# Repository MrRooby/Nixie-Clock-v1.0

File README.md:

# Nixie Clock v1.0

An ESP32-based Nixie Clock project featuring:
- Time and date display
- Temperature and humidity readings
- Gas level alarm detection
- Bluetooth control for alarm clock

## Table of Contents
1. [Introduction](#introduction)
2. [Features](#features)
3. [Hardware Setup](#hardware-setup)
4. [Bluetooth Application](#bluetooth-application)
5. [Schematic and Board Photos](#schematic-and-board-photos)
6. [Device Photos](#device-photos)
7. [**Issues**](#issues)

## Introduction
This project displays the current time, date, temperature, and humidity on Z573M Nixie tubes. It also includes a gas sensor alarm, and Bluetooth set alarm clock connectivity.

## Features
- Displays time in HH:MM format on Nixie tubes
- Shows date in DD-MM format
- Reads temperature and humidity via a DHT22 sensor
- Detects gas levels using an MQ-9 sensor
- Allows alarm configuration via Bluetooth
- Alerts with a buzzer and LEDs

## Hardware Setup
1. Nixie tubes are connected to 170V and are driven via K155ID.
2. Drivers responsible for the lamps are connected to ESP32 via Level Shifters (3.3V to 5V)
3. Two of the drivers are connected to PCF8575 I2C port expander.
4. RTC clock is connected to the board for time keeping
5. DHT and MQ-9 sensors are connected directly to the ESP32 pins.
6. Buzzer and LEDs are connected directly to the ESP32

## Bluetooth Application
*(pending)*

## Schematic and Board Photos

## Device Photos

## Issues
The device's current version suffers from a couple of mistakes or errors.
1. Mirrored Z573M library. **Temporary fix:** Lamps connected from the bottom of the board.
2. Board enters boot-loop. **Temporary fix:** Button connected between IO12 and GND. If pressed, the board exits the boot loop and functions properly.
3. Wrong MQ9 input voltage. Sensor requires 5V and connected trace supplies 3.3V. **Temporary fix:** Cable connected to 5V omitting on-board trace.
4. LED pins don't supply enough current via PCF8575 **Temporary fix:** LEDs connected directly to ESP32

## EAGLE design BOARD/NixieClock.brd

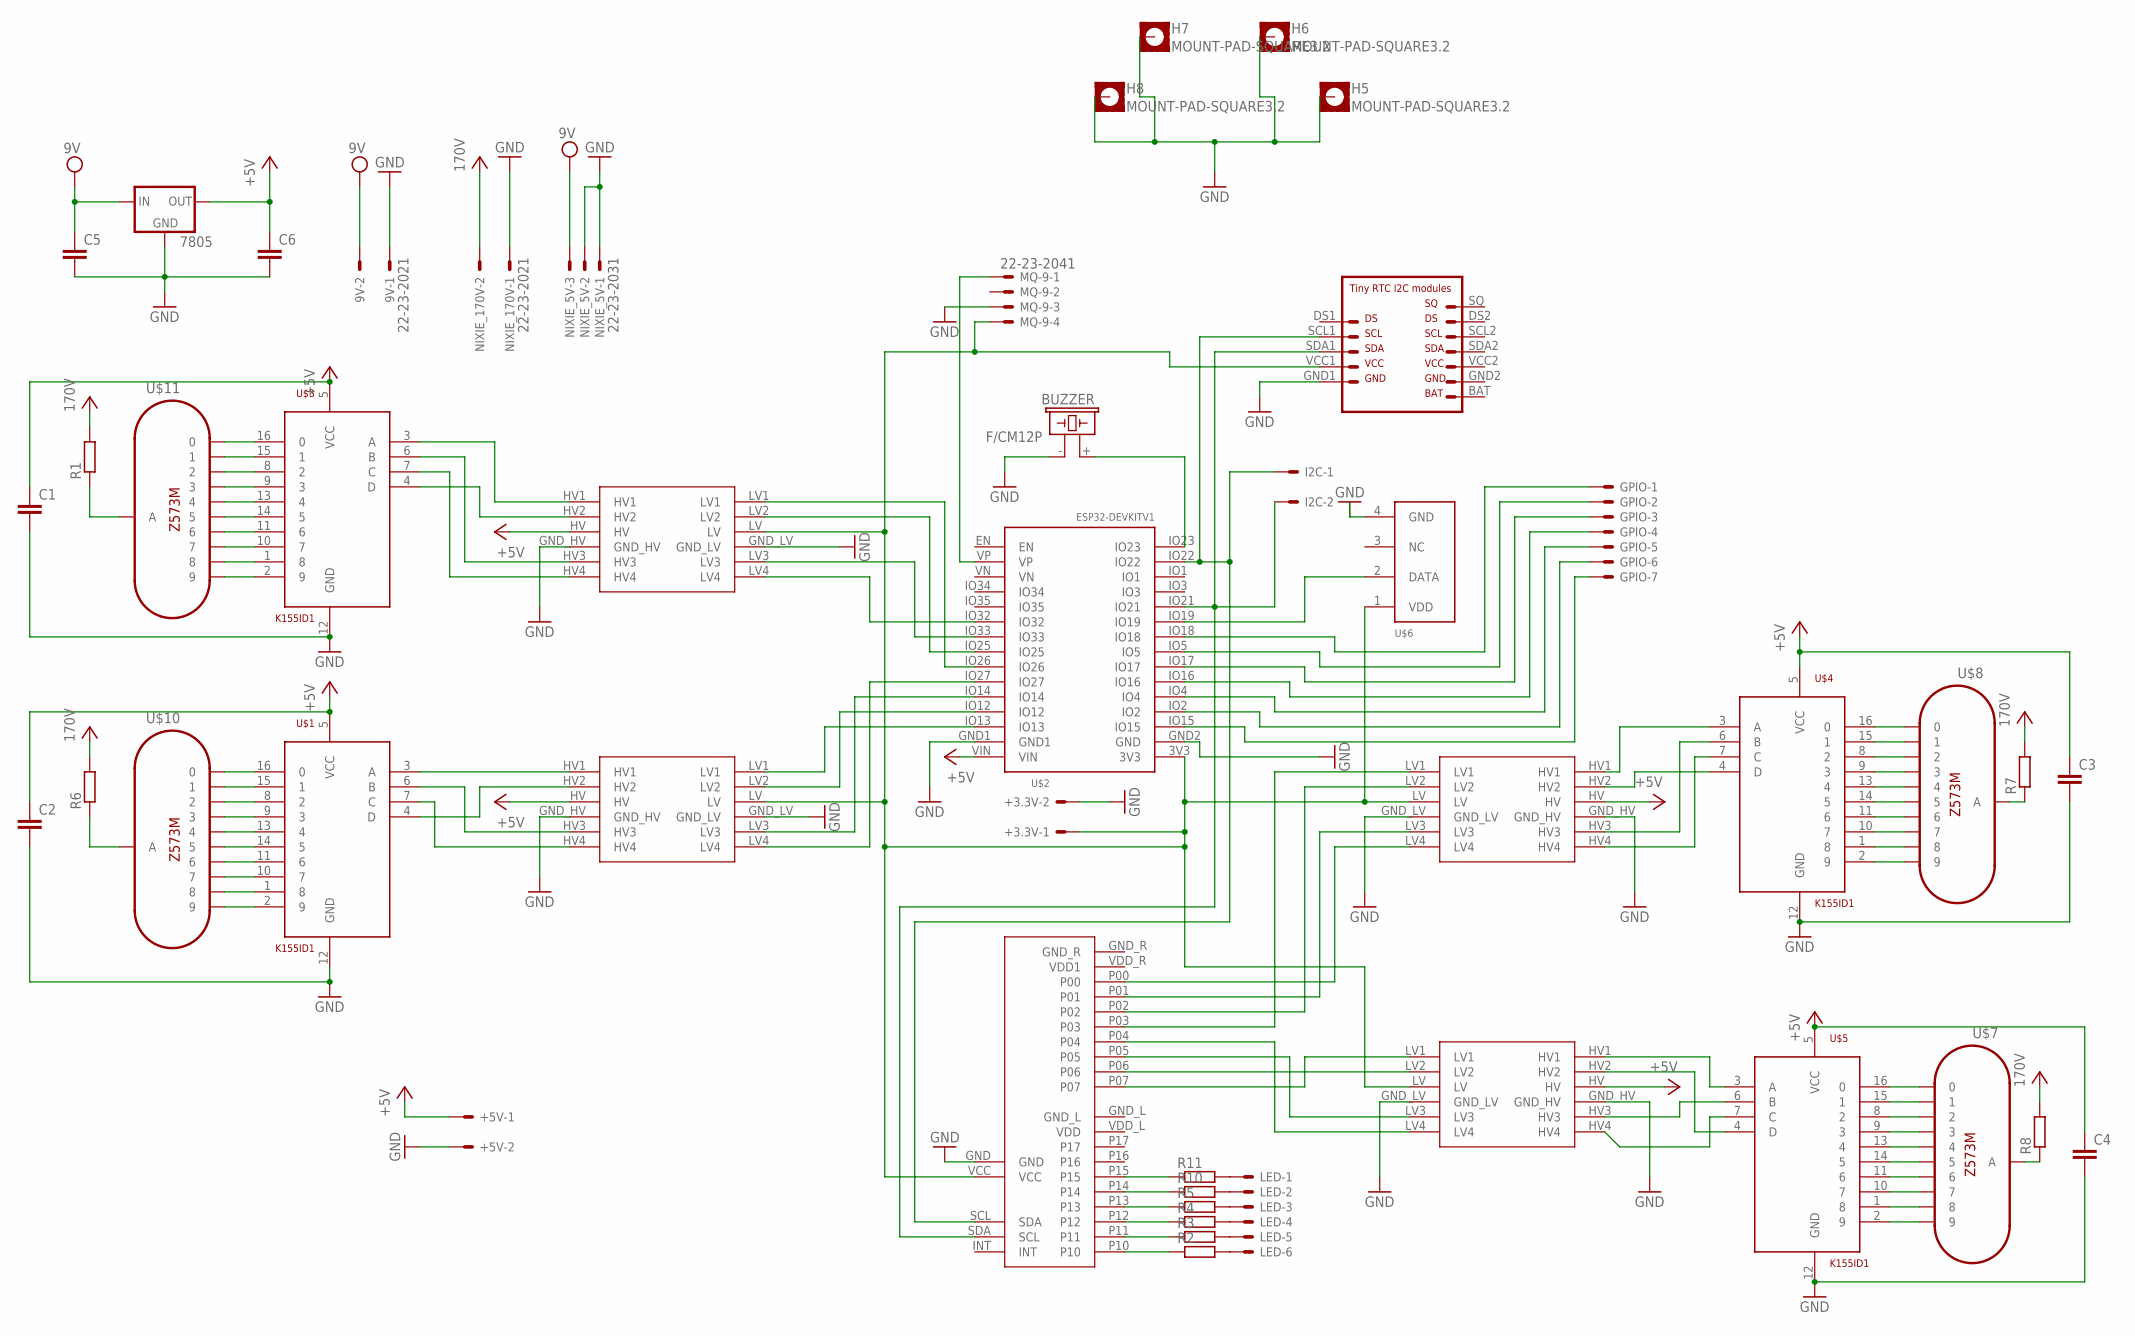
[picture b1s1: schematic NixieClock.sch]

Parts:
9V: 22-23-2021
7805: 78XXS
+3.3V, +5V: KK-156-2
BUZZER: F/CM12P
C1, C2, C3, C4, C5, C6: C2,5-3; C2.5-3
GPIO: KK-156-7
H5, H6, H7, H8: MOUNT-PAD-SQUARE3.2; 3,2-PAD-SQUARE
I2C: KK-156-2
LED: KK-156-6
MQ-9: 22-23-2041; MPN wyświetlacz I2C
NIXIE_5V: 22-23-2031
NIXIE_170V: 22-23-2021
R1, R2, R3, R4, R5, R6, R7, R8, R10, R11: R-EU_0204/7; 0204/7
STEP_UP_$: LEVEL-CONVERTER
U$1, U$3, U$4, U$5: K155ID1; DIP16-2.54-19.2X7.62MM
U$2: ESP32DEVKITV1; ESP32-DEVKITV1
U$6: DHT11
U$7, U$8, U$10, U$11: Z573M
U$9: RTC
U$12, U$13, U$15: LEVEL-CONVERTER
U$16: PCF8575

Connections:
3.3V: +3.3V.1, MQ-9.4, STEP_UP_$.LV, U$2.3V3, U$6.1 (VDD), U$9.VCC1, U$12.LV, U$13.LV, U$15.LV, U$16.VCC
170V: 9V.2, 7805.IN, C5.1, NIXIE_5V.3, NIXIE_170V.2, R1.2, R6.2, R7.2, R8.2
+5V: 7805.OUT, +5V.1, C1.1, C2.1, C3.1, C4.1, C6.1, STEP_UP_$.HV, U$1.5 (VCC), U$2.VIN, U$3.5 (VCC), U$4.5 (VCC), U$5.5 (VCC), U$12.HV, U$13.HV, U$15.HV
GND: 9V.1, 7805.GND, +3.3V.2, +5V.2, BUZZER.- (2), C1.2, C2.2, C3.2, C4.2, C5.2, C6.2, H5.B3,2, H6.B3,2, H7.B3,2, H8.B3,2, MQ-9.3, NIXIE_5V.1, NIXIE_5V.2, NIXIE_170V.1, STEP_UP_$.GND_HV, STEP_UP_$.GND_LV, U$1.12 (GND), U$2.GND1, U$2.GND2 (GND), U$3.12 (GND), U$4.12 (GND), U$5.12 (GND), U$6.4 (GND), U$9.GND1, U$12.GND_HV, U$12.GND_LV, U$13.GND_HV, U$13.GND_LV, U$15.GND_HV, U$15.GND_LV, U$16.GND
unnamed: STEP_UP_$.HV1, U$5.3 (A)
unnamed: STEP_UP_$.HV2, U$5.4 (D)
unnamed: STEP_UP_$.HV3, U$5.6 (B)
unnamed: STEP_UP_$.HV4, U$5.7 (C)
unnamed: U$15.LV4, U$16.P00
unnamed: U$4.3 (A), U$15.HV1
unnamed: U$4.4 (D), U$15.HV2
unnamed: U$4.6 (B), U$15.HV3
unnamed: U$3.3 (A), U$13.HV1
unnamed: U$3.4 (D), U$13.HV2
unnamed: U$3.6 (B), U$13.HV3
unnamed: U$3.7 (C), U$13.HV4
unnamed: U$1.3 (A), U$12.HV1
unnamed: U$1.4 (D), U$12.HV2
unnamed: U$1.6 (B), U$12.HV3
unnamed: U$1.7 (C), U$12.HV4
unnamed: U$3.16 (0), U$11.K0 (0)
unnamed: U$3.15 (1), U$11.K1 (1)
unnamed: U$3.8 (2), U$11.K2 (2)
unnamed: U$3.9 (3), U$11.K3 (3)
unnamed: U$3.13 (4), U$11.K4 (4)
unnamed: U$3.14 (5), U$11.K5 (5)
unnamed: U$3.11 (6), U$11.K6 (6)
unnamed: U$3.10 (7), U$11.K7 (7)
unnamed: U$3.1 (8), U$11.K8 (8)
unnamed: U$3.2 (9), U$11.K9 (9)
unnamed: U$1.16 (0), U$10.K0 (0)
unnamed: U$1.15 (1), U$10.K1 (1)
unnamed: U$1.8 (2), U$10.K2 (2)
unnamed: U$1.9 (3), U$10.K3 (3)
unnamed: U$1.13 (4), U$10.K4 (4)
unnamed: U$1.14 (5), U$10.K5 (5)
unnamed: U$1.11 (6), U$10.K6 (6)
unnamed: U$1.10 (7), U$10.K7 (7)
unnamed: U$1.1 (8), U$10.K8 (8)
unnamed: U$1.2 (9), U$10.K9 (9)
unnamed: U$5.16 (0), U$7.K0 (0)
unnamed: U$5.15 (1), U$7.K1 (1)
unnamed: U$5.8 (2), U$7.K2 (2)
unnamed: U$5.9 (3), U$7.K3 (3)
unnamed: U$5.13 (4), U$7.K4 (4)
unnamed: U$5.14 (5), U$7.K5 (5)
unnamed: U$5.11 (6), U$7.K6 (6)
unnamed: U$5.10 (7), U$7.K7 (7)
unnamed: U$5.1 (8), U$7.K8 (8)
unnamed: U$5.2 (9), U$7.K9 (9)
unnamed: U$4.2 (9), U$8.K9 (9)
unnamed: U$4.1 (8), U$8.K8 (8)
unnamed: U$4.10 (7), U$8.K7 (7)
unnamed: U$4.11 (6), U$8.K6 (6)
unnamed: U$4.14 (5), U$8.K5 (5)
unnamed: U$4.13 (4), U$8.K4 (4)
unnamed: U$4.9 (3), U$8.K3 (3)
unnamed: U$4.8 (2), U$8.K2 (2)
unnamed: U$4.15 (1), U$8.K1 (1)
unnamed: U$4.16 (0), U$8.K0 (0)
unnamed: U$15.LV3, U$16.P01
unnamed: U$2.IO27, U$12.LV4
unnamed: I2C.1, U$2.IO22, U$9.SCL1, U$16.SCL (SDA)
unnamed: I2C.2, U$2.IO21, U$9.SDA1, U$16.SDA (SCL)
unnamed: BUZZER.+ (1), U$2.IO23
unnamed: U$15.LV2, U$16.P02
unnamed: MQ-9.1, U$2.VP
unnamed: U$15.LV1, U$16.P03
unnamed: STEP_UP_$.LV4, U$16.P04
unnamed: STEP_UP_$.LV3, U$16.P05
unnamed: STEP_UP_$.LV2, U$16.P06
unnamed: STEP_UP_$.LV1, U$16.P07
unnamed: U$2.IO19, U$6.2 (DATA)
unnamed: GPIO.1, U$2.IO18
unnamed: GPIO.2, U$2.IO5
unnamed: U$2.IO26, U$13.LV1
unnamed: U$2.IO25, U$13.LV2
unnamed: U$2.IO33, U$13.LV3
unnamed: U$2.IO32, U$13.LV4
unnamed: U$2.IO13, U$12.LV1
unnamed: U$2.IO12, U$12.LV2
unnamed: U$2.IO14, U$12.LV3
unnamed: R8.1, U$7.A
unnamed: R7.1, U$8.A
unnamed: R6.1, U$10.A
unnamed: R1.1, U$11.A
unnamed: GPIO.3, U$2.IO17
unnamed: R2.1, U$16.P10
unnamed: R3.1, U$16.P11
unnamed: R4.1, U$16.P12
unnamed: R5.1, U$16.P13
unnamed: R10.1, U$16.P14
unnamed: R11.1, U$16.P15
unnamed: LED.1, R11.2
unnamed: LED.2, R10.2
unnamed: LED.3, R5.2
unnamed: LED.4, R4.2
unnamed: LED.5, R3.2
unnamed: LED.6, R2.2
unnamed: GPIO.4, U$2.IO16
unnamed: GPIO.5, U$2.IO4
unnamed: GPIO.6, U$2.IO2
unnamed: GPIO.7, U$2.IO15
unnamed: U$4.7 (C), U$15.HV4

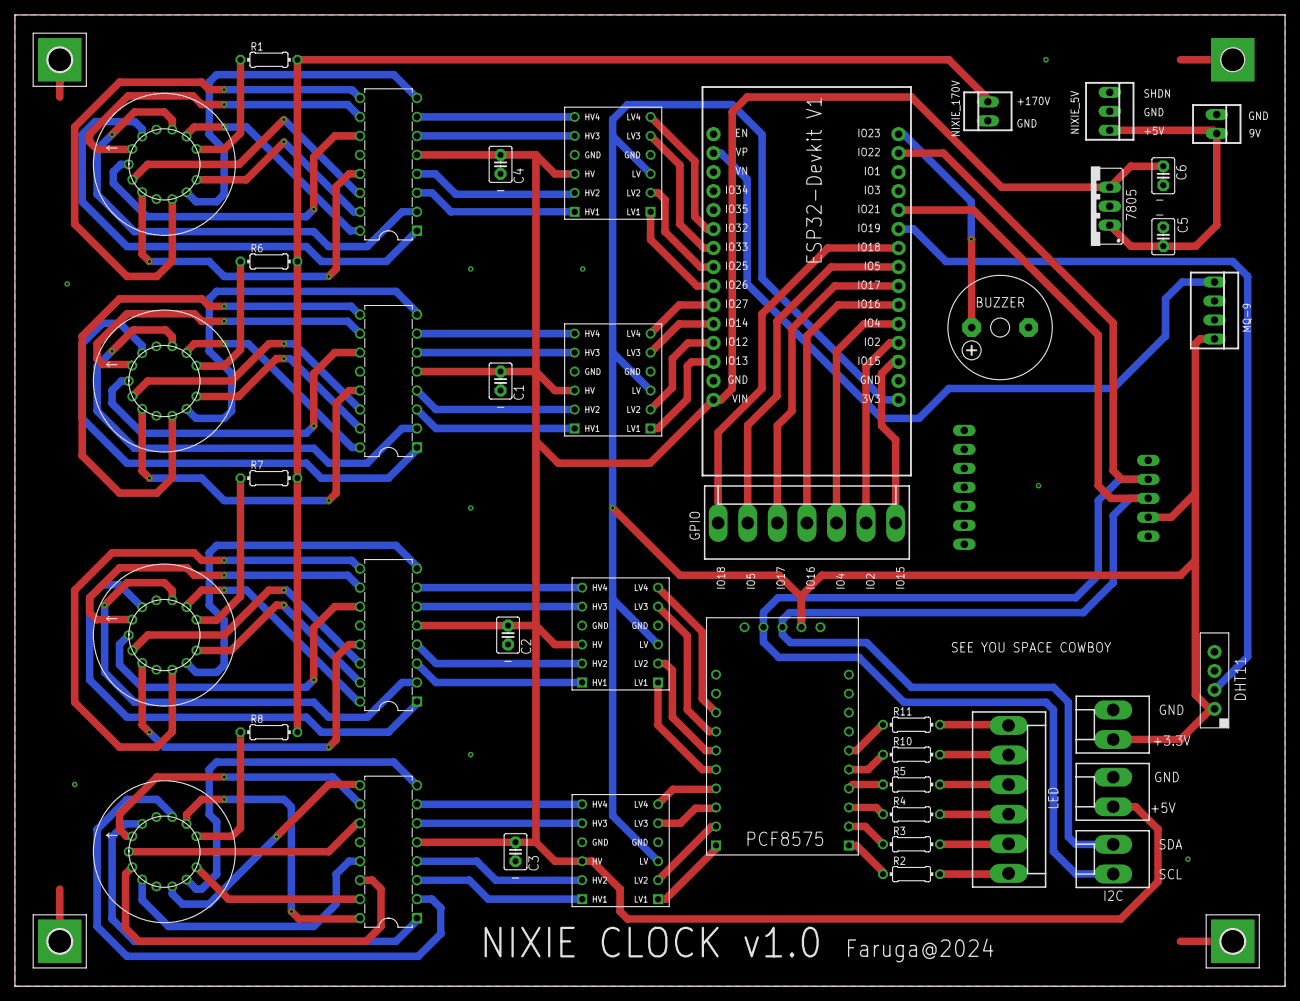
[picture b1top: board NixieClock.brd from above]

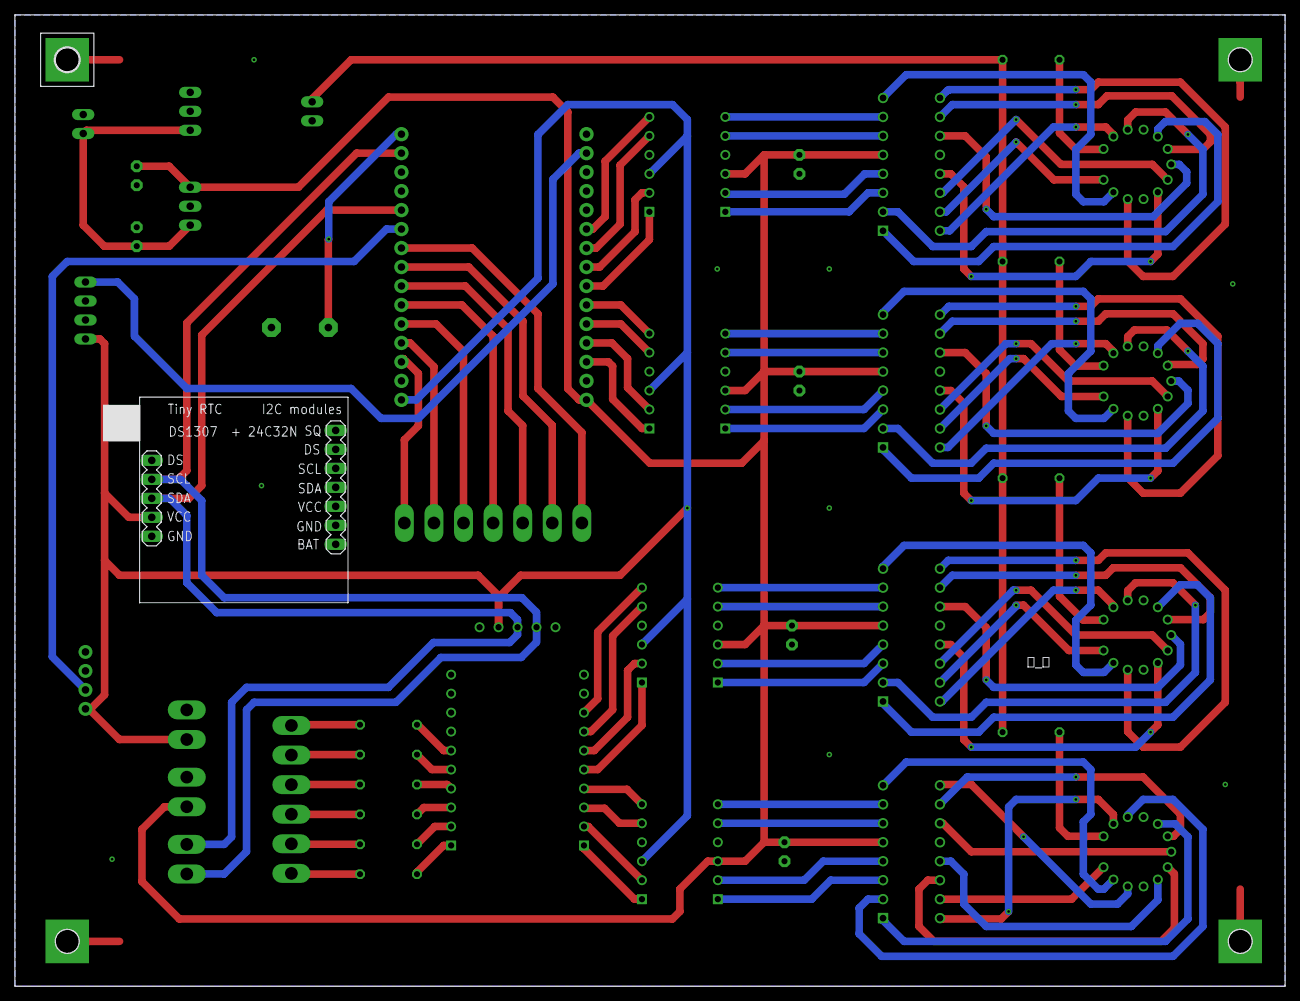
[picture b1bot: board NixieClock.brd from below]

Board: 2 copper layers, 170.0 x 130.0 mm, 47 parts (2 on the bottom side), 104 nets.

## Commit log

2024-12-22 Added .sch and .brd files
2024-12-22 ixed K155ID1 pin definitions. Added functions to display temperature and humidity on the nixie lamps
2024-12-22 implemented OOP for lamps and sensors to improve code clarity
2024-12-22 added class for handling and parsing time data from the RTC to display on the lamps. Changed all uint_least8_t variables to unsigned int due to error with division
2024-12-25 TODO: Implement CO2 read function, implement APP, implement alarm clock with a snooze button
2024-12-25 env support
2025-01-02 changed blynk implementation to custom bluetooth connection to the MIT app inventor. Final version for tests
2025-01-06 added MQ9 support. Fixed all other issues accept DHT11 mismatched data
2025-01-07 minor tweaks
2025-01-08 added blinking leds when gas alarm is activated, fixed temperature and humidity displaying
2025-01-10 updated DHT sensor type to DHT22, adjusted sensor refresh rate, and commented out temperature and humidity display
